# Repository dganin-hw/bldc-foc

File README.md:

# Контроллер BLDC с FOC на STM32

**Своя силовая плата, плата магнитного энкодера и печатный стенд. Дальше тот же канал
ляжет в основу четырёхканального ESC для квадрокоптера.**

[Основная плата](hardware/dev-board/README.md) ·
[Плата энкодера](hardware/encoder-board/README.md) ·
[Стенд](hardware/stand/README.md) ·
[Прошивка](firmware/README.md) ·
[4-in-1 ESC](hardware/esc-4in1/README.md) ·
[Теория FOC](docs/foc-theory.md)

Делаю управление бесщёточным мотором целиком: силовую часть, измерение токов, угол
ротора и векторное управление (FOC). Сначала стенд на один мотор. Когда измерения
сойдутся с расчётом, тот же канал перейдёт в 4-in-1 ESC.

**Сейчас:** обе платы разведены, файлы для производства и перечни компонентов готовы,
механика стенда готова к печати. В прошивке каркас, параметры и тесты. На реальном
моторе ещё не запускал.

## Что готово

| Часть | Что это | Состояние |
|---|---|---|
| [Основная плата](hardware/dev-board/README.md) | STM32G431, DRV8323RS, трёхфазный мост, три шунта, питание и интерфейсы. 108 × 81 мм, 4 слоя | схема, разводка, файлы для производства |
| [Плата энкодера](hardware/encoder-board/README.md) | AS5047P, SPI, питание 3,3 В. 32 × 28 мм, 2 слоя | схема, разводка, файлы для производства |
| [Стенд](hardware/stand/README.md) | основание, крепления плат и мотора, регулируемая опора энкодера, держатель магнита | STL, STEP и инструкция, ещё не напечатан |
| [Прошивка](firmware/README.md) | библиотека на C, конфигурация ШИМ, параметры моторов, тесты | каркас, FOC ещё не написан |
| [4-in-1 ESC](hardware/esc-4in1/README.md) | схема на два STM32G474, распределение выводов, проверка размещения | черновик, не для производства |

Проверки ERC и DRC в KiCad 10 проходят без ошибок на обеих платах. Это проверка
файлов: ток, нагрев и защиты проверяются на собранном стенде.

## Как устроено

Угол ротора приходит с платы энкодера по SPI, токи фаз снимаются с шунтов через
усилители DRV8323. FOC переводит токи в координаты ротора, регулирует их и выдаёт
скважности ШИМ. Драйвер открывает шесть MOSFET трёх полумостов. Авария драйвера
(nFAULT) заведена на вход BKIN таймера и выключает ШИМ аппаратно.

Быстрый цикл привязан к ШИМ 48 кГц и запуску АЦП от того же таймера. Команды и
телеметрия идут вне этого цикла. Энкодер нужен на первых запусках и как эталон, когда
дойдёт до оценки угла без датчика.

Питание стенда 9-16 В, обычно 12 В. На первых включениях ток фазы ограничен 1 А:
этот предел держат прошивка и блок питания, а не плата.

## Основная плата

Четыре слоя: микроконтроллер, драйвер, мост, три канала измерения тока и питание
логики. На плате 36 контрольных площадок: на каждый затвор и исток, ШИМ, токи,
питание. Силовая часть отделена перемычкой, поэтому плату можно запускать по шагам.

[Описание](hardware/dev-board/README.md) ·
[Сборка и первое включение](hardware/dev-board/bring-up.md) ·
[Схема PDF](hardware/dev-board/documentation/SCHEMATIC.pdf) ·
[Файлы для производства](hardware/dev-board/manufacturing/README.md) ·
[CubeMX](hardware/dev-board/cubemx/CubeMX.ioc)

## Плата энкодера

Отдельная маленькая плата, чтобы выставить датчик по оси магнита и подобрать зазор.
Магнит вращается вместе с ротором, плата неподвижна. К основной плате подключается
шестиконтактным кабелем.

[Описание](hardware/encoder-board/README.md) ·
[Схема PDF](hardware/encoder-board/documentation/SCHEMATIC.pdf) ·
[Файлы для производства](hardware/encoder-board/manufacturing/README.md)

## Стенд

Печать из PETG: 11 моделей STL, общая сборка в STEP, пробник посадок, щуп для зазора
и перечень крепежа. Мотор T-Motor MN2212 V2.0 KV920, работа без пропеллера.

[Описание и печать](hardware/stand/README.md) ·
[Сборка и крепёж](hardware/stand/assembly.md) ·
[Лист деталей PDF](hardware/stand/print-layout.pdf)

## Основные компоненты

| Компонент | Зачем |
|---|---|
| STM32G431CBT6 | Cortex-M4F 170 МГц, таймер TIM1 с dead-time и аварийным входом, два АЦП с запуском от таймера |
| DRV8323RSRGZT | драйвер шести затворов, три усилителя тока, диагностика по SPI, свой понижающий преобразователь |
| 6 × PSMN7R0-60YS,115 | N-MOSFET моста, 60 В, корпус LFPAK56 |
| 3 × WSK2512R0200FEA | шунты 20 мОм с отдельными измерительными выводами |
| AS5047P-ATSM | магнитный энкодер, 14 бит, на отдельной плате |
| AP2112K-3.3TRG1 | 3,3 В для логики |
| SRN6045TA-330M и SS16 | дроссель и диод понижающего преобразователя |
| IRFR5305TRPBF | защита входа от переполюсовки |
| SMBJ18A | TVS-диод от коротких выбросов. Энергию торможения он не поглощает |
| NCP18XH103F03RB | термистор, температура платы |
| Eaton BK1/S501-2-R | предохранитель 2 А на входе. Мост он не защищает |

Полный перечень с артикулами и кодами LCSC: [основная плата](hardware/dev-board/manufacturing/bom/BOM.csv),
[плата энкодера](hardware/encoder-board/manufacturing/bom/BOM.csv).

## Прошивка

Пишу на C99. Математика FOC отделена от регистров, поэтому один и тот же код
собирается на ПК для тестов и кросс-компилятором под Cortex-M4F. В GitHub Actions на
каждый push запускаются тесты на ПК и сборка под ARM.

Нужны CMake 3.20 или новее и компилятор C. Из корня репозитория:

```sh
cmake -S firmware -B build -DCMAKE_BUILD_TYPE=Debug
cmake --build build --parallel
ctest --test-dir build --output-on-failure
```

Сейчас готовы вспомогательные функции, конфигурация ШИМ, параметры моторов и тесты.
Преобразования Кларка и Парка, PI-регуляторы, модулятор, модель мотора, драйверы и
наблюдатель на очереди.

[Подробнее о прошивке](firmware/README.md) ·
[Архитектура прошивки](docs/firmware-architecture.md) ·
[Теория FOC](docs/foc-theory.md)

## План

- [ ] **Этап 0. FOC на модели мотора.** Каркас, тесты и CI уже есть. Дальше
  преобразования, SVPWM, PI и модель мотора на ПК.
- [x] **Этап 1. Основная плата и плата энкодера.** Схема, разводка, файлы для
  производства, механика стенда.
- [ ] **Этап 2. Запуск платы и FOC с энкодером.** Питание, защиты, калибровка токов,
  окно АЦП, токовый контур на стенде, нагрев.
- [ ] **Этап 3. Работа без датчика.** Наблюдатель с PLL, сравнение оценки угла с
  энкодером, переход на дрон-мотор.
- [ ] **Этап 4. Интерфейс дрона.** Приём DShot600, телеметрия, защиты, проверка с
  покупным полётным контроллером.
- [ ] **Этап 5. Плата 4-in-1.** Сначала один канал, потом остальные три.
- [ ] **Этап 6. Квадрокоптер.** Проверки на земле без пропеллеров, полёт на привязи.

Почему полётный контроллер покупной и как всё связано, описано в
[архитектуре системы](docs/system-architecture.md). Правила безопасности на стенде:
[docs/safety.md](docs/safety.md).

## Структура репозитория

```text
bldc-foc/
├── assets/                картинки для README
├── docs/                  теория FOC, архитектура, план выводов, безопасность
├── firmware/              библиотека на C, тесты и CMake
├── hardware/
│   ├── dev-board/         основная плата: KiCad, CubeMX, документация, производство
│   ├── encoder-board/     плата энкодера
│   ├── stand/             испытательный стенд: STL, STEP, сборка
│   └── esc-4in1/          черновик четырёхканального ESC
├── sources/               ссылки на документацию производителей
└── .github/workflows/     сборка и тесты в GitHub Actions
```

Проекты KiCad открываются в KiCad 10. Лицензия на проект пока не выбрана,
сторонние материалы описаны в [LICENSES.md](LICENSES.md), документация производителей
в [sources/README.md](sources/README.md).

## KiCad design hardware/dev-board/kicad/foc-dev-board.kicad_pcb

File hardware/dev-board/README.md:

# Основная плата

Плата управления одним бесколлекторным мотором: STM32G431, драйвер DRV8323RS,
трёхфазный мост на шести MOSFET и три шунта для измерения токов. Всё, что нужно
мерить на стенде, выведено на контрольные площадки.

*3D-вид из KiCad. Шунты R30-R32 показаны без 3D-модели.*

*Нижняя сторона по Gerber-файлам: распиновка разъёмов на шелкографии.*

## Коротко

| Параметр | Значение |
|---|---|
| Размер | 108 × 81 мм, 4 слоя, FR-4 1,6 мм |
| Компоненты | 149 позиций, из них 109 устанавливаются, 36 контрольных площадок и 4 отверстия M3 |
| Трассировка | 2598 сегментов дорожек, 300 переходных отверстий, земля на всех четырёх слоях |
| Питание | 12 В номинально, рабочий диапазон 9-16 В |
| Ток фазы на первых запусках | до 1 А (ограничение в прошивке и на блоке питания) |
| Измерение тока | шунты 20 мОм, усиление 40, 0,8 В/А, линейный диапазон около ±1,75 А |
| ШИМ | 48 кГц, TIM1, центрированный, dead-time около 400 нс |

## Схема по листам

| Лист | Что на нём |
|---|---|
| 01 Power | вход, предохранитель 2 А, защита от переполюсовки, понижающий преобразователь 5 В, LDO 3,3 В |
| 02 MCU | STM32G431CBT6 в LQFP48, развязка питания, BOOT0, RESET, светодиоды |
| 03 Driver | DRV8323RS, зарядовый насос, SPI, ENABLE, nFAULT, фильтры АЦП |
| 04 Inverter | шесть MOSFET PSMN7R0-60YS, затворные резисторы, три четырёхвыводных шунта |
| 05 Interfaces | мотор, энкодер, SWD, UART, DShot, делитель напряжения шины, термистор |
| 06 Testpoints | 36 контрольных площадок и четыре крепёжных отверстия |

Назначение выводов STM32 описано в [плане выводов](../../docs/pin-plan.md),
конфигурация периферии лежит в [`cubemx/CubeMX.ioc`](cubemx/CubeMX.ioc).

## Как устроено питание

`J1 → F1 → Q7 → VIN_PROTECTED`: вход через предохранитель 2 А и P-MOSFET от переполюсовки.
От `VIN_PROTECTED` работает понижающий преобразователь DRV8323 (5 В) и дальше LDO AP2112
(3,3 В для STM32 и энкодера).

- **JP1** подключает `VIN_PROTECTED` к шине `VM`, то есть к мосту и питанию драйвера.
  С открытой JP1 можно спокойно проверить питание логики и прошить МК.
- **JP2** разрешает управлять ENABLE драйвера с МК. Без перемычки резистор R14 держит
  ENABLE в нуле.
- **SW2** отключает драйвер, пока кнопка нажата. Это не защёлка: после отпускания
  прошивка не должна включаться сама.
- **nFAULT** драйвера заведён на PA12 и на вход BKIN таймера TIM1, чтобы ШИМ выключался
  аппаратно.
- **J7** выводит шину `VM` для внешней нагрузки при опытах с торможением. TVS-диод
  SMBJ18A гасит только короткие выбросы и не рассчитан на энергию торможения.

## Разъёмы

| Разъём | Назначение |
|---|---|
| J1 | питание 12 В |
| J2 | фазы мотора A, B, C |
| J3 | энкодер: 3,3 В, GND, SCK, MISO, MOSI, CS |
| J4 | SWD: VTREF, GND, SWDIO, SWCLK, NRST |
| J5 | UART: 3,3 В, GND, TX, RX |
| J6 | DShot и GND |
| J7 | шина VM для внешней нагрузки |

Все сигналы 3,3 В. Контакты питания на разъёмах - выход платы или VTREF, а не вход.

## Контрольные площадки

| Площадки | Что на них |
|---|---|
| TP1-TP3 | GND |
| TP4, TP5 | VIN_PROTECTED и VM, до и после JP1 |
| TP6, TP7, TP8 | 5 В, 3,3 В и аналоговые 3,3 В |
| TP9-TP12 | ENABLE, nFAULT, сигнал замера времени цикла, MISO |
| TP13-TP18 | шесть сигналов ШИМ от STM32 |
| TP19, TP20, TP21 | сигналы токов фаз A, B, C на входах АЦП |
| TP22, TP23 | напряжение шины и температура |
| TP24 | внутреннее питание DVDD драйвера |
| TP25-TP36 | затвор и исток верхнего и нижнего ключа каждой фазы |

Землю обычного осциллографа подключать только к GND, а не к фазе или истоку верхнего
ключа. Для таких точек нужен дифференциальный щуп.

## Файлы

- [`kicad/`](kicad/) - проект KiCad 10: схема, плата и библиотеки проекта. Открывать
  `foc-dev-board.kicad_pro`, копировать нужно всю папку.
- [`documentation/SCHEMATIC.pdf`](documentation/SCHEMATIC.pdf) - схема, 7 листов.
- [`documentation/ASSEMBLY.pdf`](documentation/ASSEMBLY.pdf) - сборочный чертёж, верхняя сторона.
- [`manufacturing/`](manufacturing/) - Gerber, сверловка, перечень компонентов и координаты.
- [`mechanical/foc-dev-board.step`](mechanical/foc-dev-board.step) - 3D-модель платы с компонентами.
- [`cubemx/`](cubemx/) - конфигурация STM32CubeMX и отчёт по ней.

## Что проверить на собранной плате

Проверки ERC и DRC в KiCad проходят без ошибок, но это проверка файлов, а не работы платы.
Перед запуском мотора нужно:

1. **Ток и защиту.** Предел 1 А задаётся прошивкой и блоком питания. Минимальный порог
   защиты DRV8323 (0,25 В на шунте) с шунтом 20 мОм соответствует 12,5 А, поэтому он не
   заменяет программный предел. Предохранитель 2 А стоит на входе и фазный ток не ограничивает.
2. **Окно АЦП.** Ток A и C измеряет ADC1, ток B - ADC2, это не одновременная выборка.
   При скважности 97% нижний ключ открыт всего 625 нс, а dead-time 400 нс плюс
   установление усилителя (при усилении 40 по документации около 1,2 мкс) туда не
   помещаются. Окно выборки и предел скважности нужно проверить осциллографом.
3. **Включение и аварийное отключение.** Запрет самозапуска, ручное повторное включение
   после аварии, работа BKIN и поведение при остановке отладчиком.
4. **Коммутацию.** Начать с умеренного тока затворов DRV8323, проверить напряжение на
   затворах, звон и отсутствие сквозного тока.
5. **Нагрев.** LDO AP2112 при 150 мА рассеивает около 0,25 Вт, ключи и шунты проверить
   термопарой на реальном токе.

Пошаговый порядок описан в [памятке по сборке и первому включению](bring-up.md).

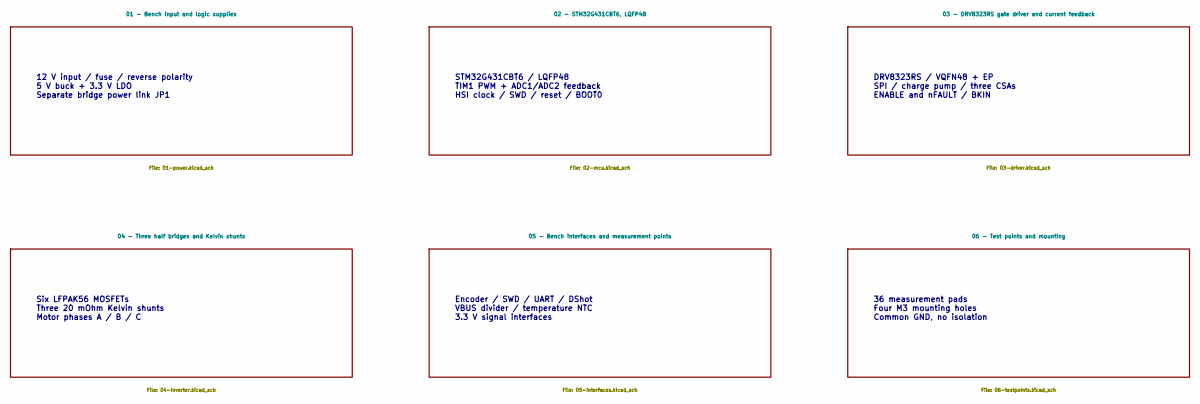
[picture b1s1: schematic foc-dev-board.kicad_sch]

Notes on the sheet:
12 V input / fuse / reverse polarity 5 V buck + 3.3 V LDO Separate bridge power link JP1
Encoder / SWD / UART / DShot VBUS divider / temperature NTC 3.3 V signal interfaces
Six LFPAK56 MOSFETs Three 20 mOhm Kelvin shunts Motor phases A / B / C
36 measurement pads Four M3 mounting holes Common GND, no isolation
DRV8323RS / VQFN48 + EP SPI / charge pump / three CSAs ENABLE and nFAULT / BKIN
STM32G431CBT6 / LQFP48 TIM1 PWM + ADC1/ADC2 feedback HSI clock / SWD / reset / BOOT0

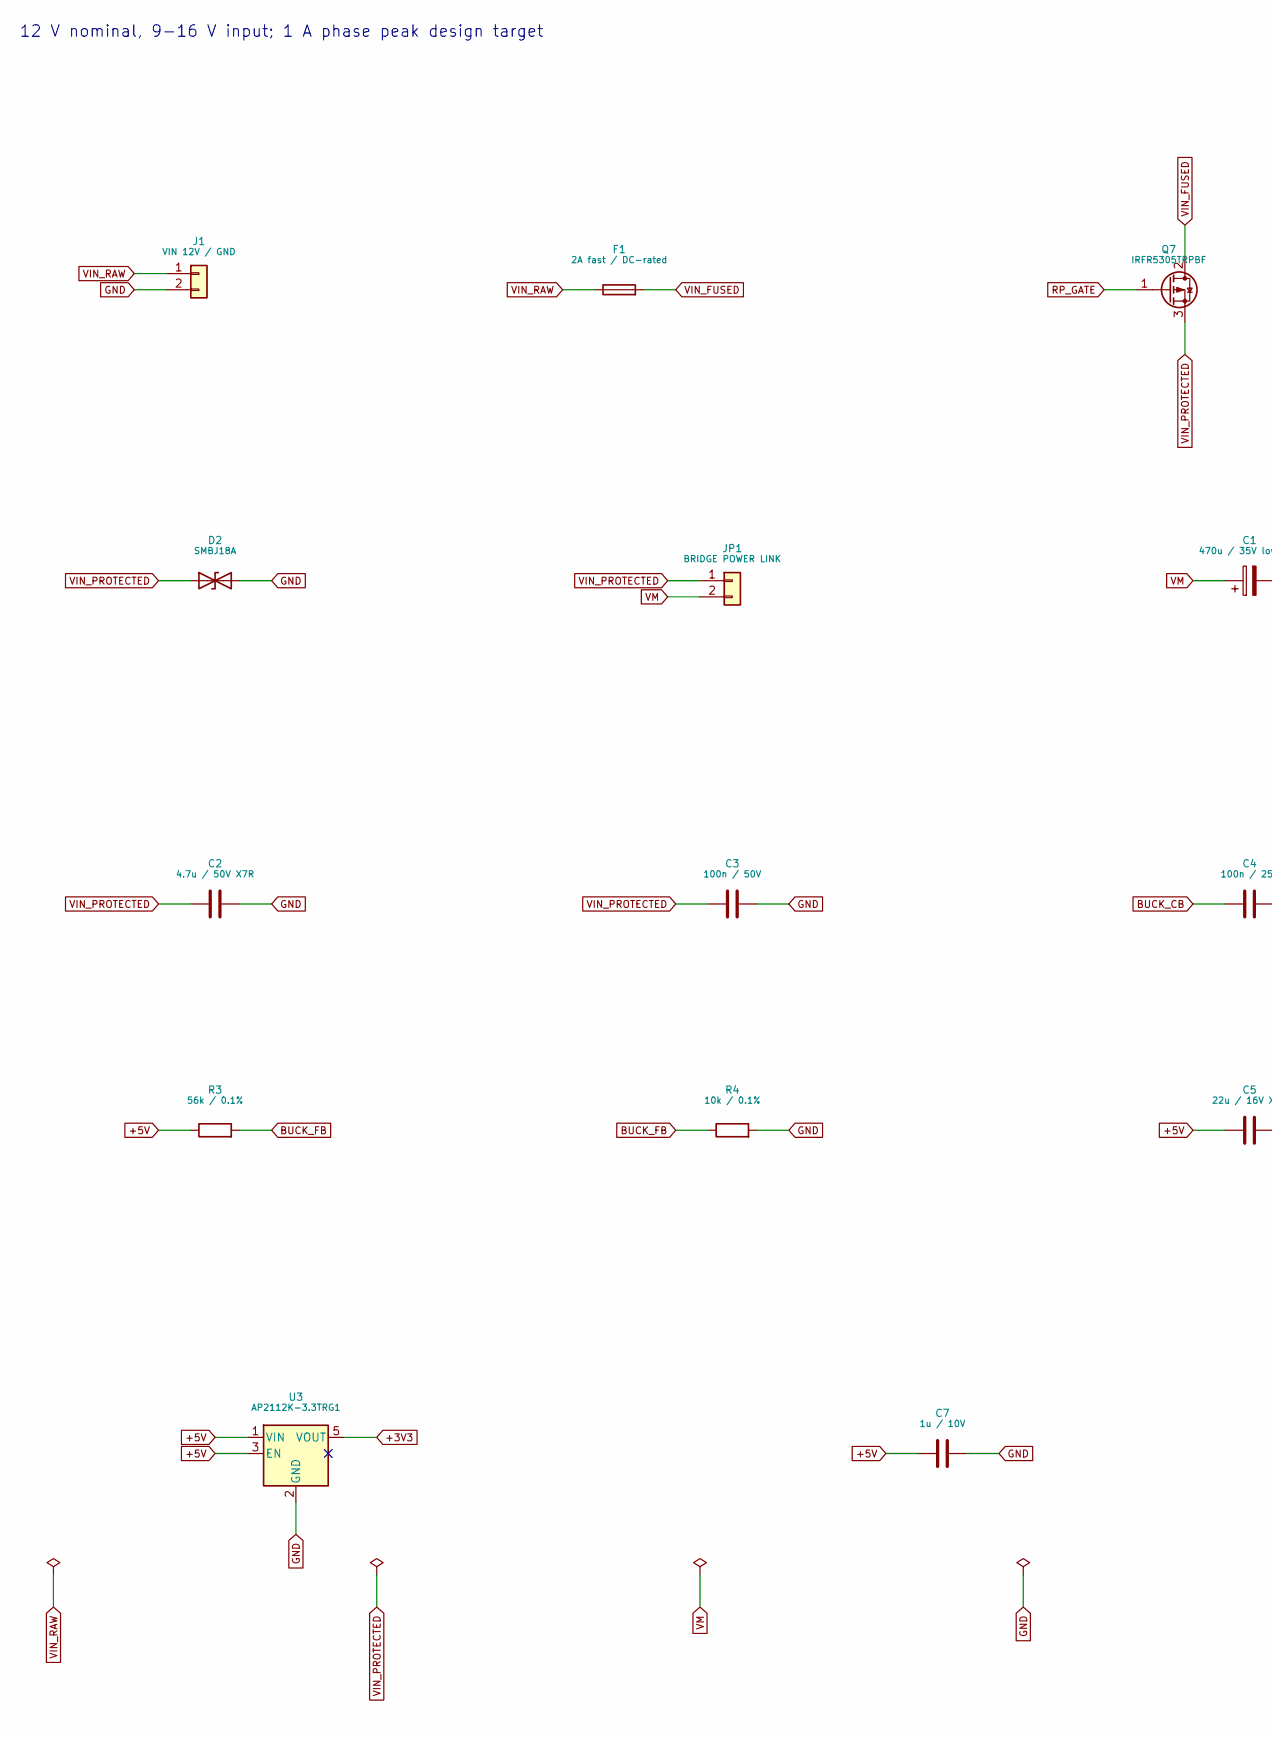
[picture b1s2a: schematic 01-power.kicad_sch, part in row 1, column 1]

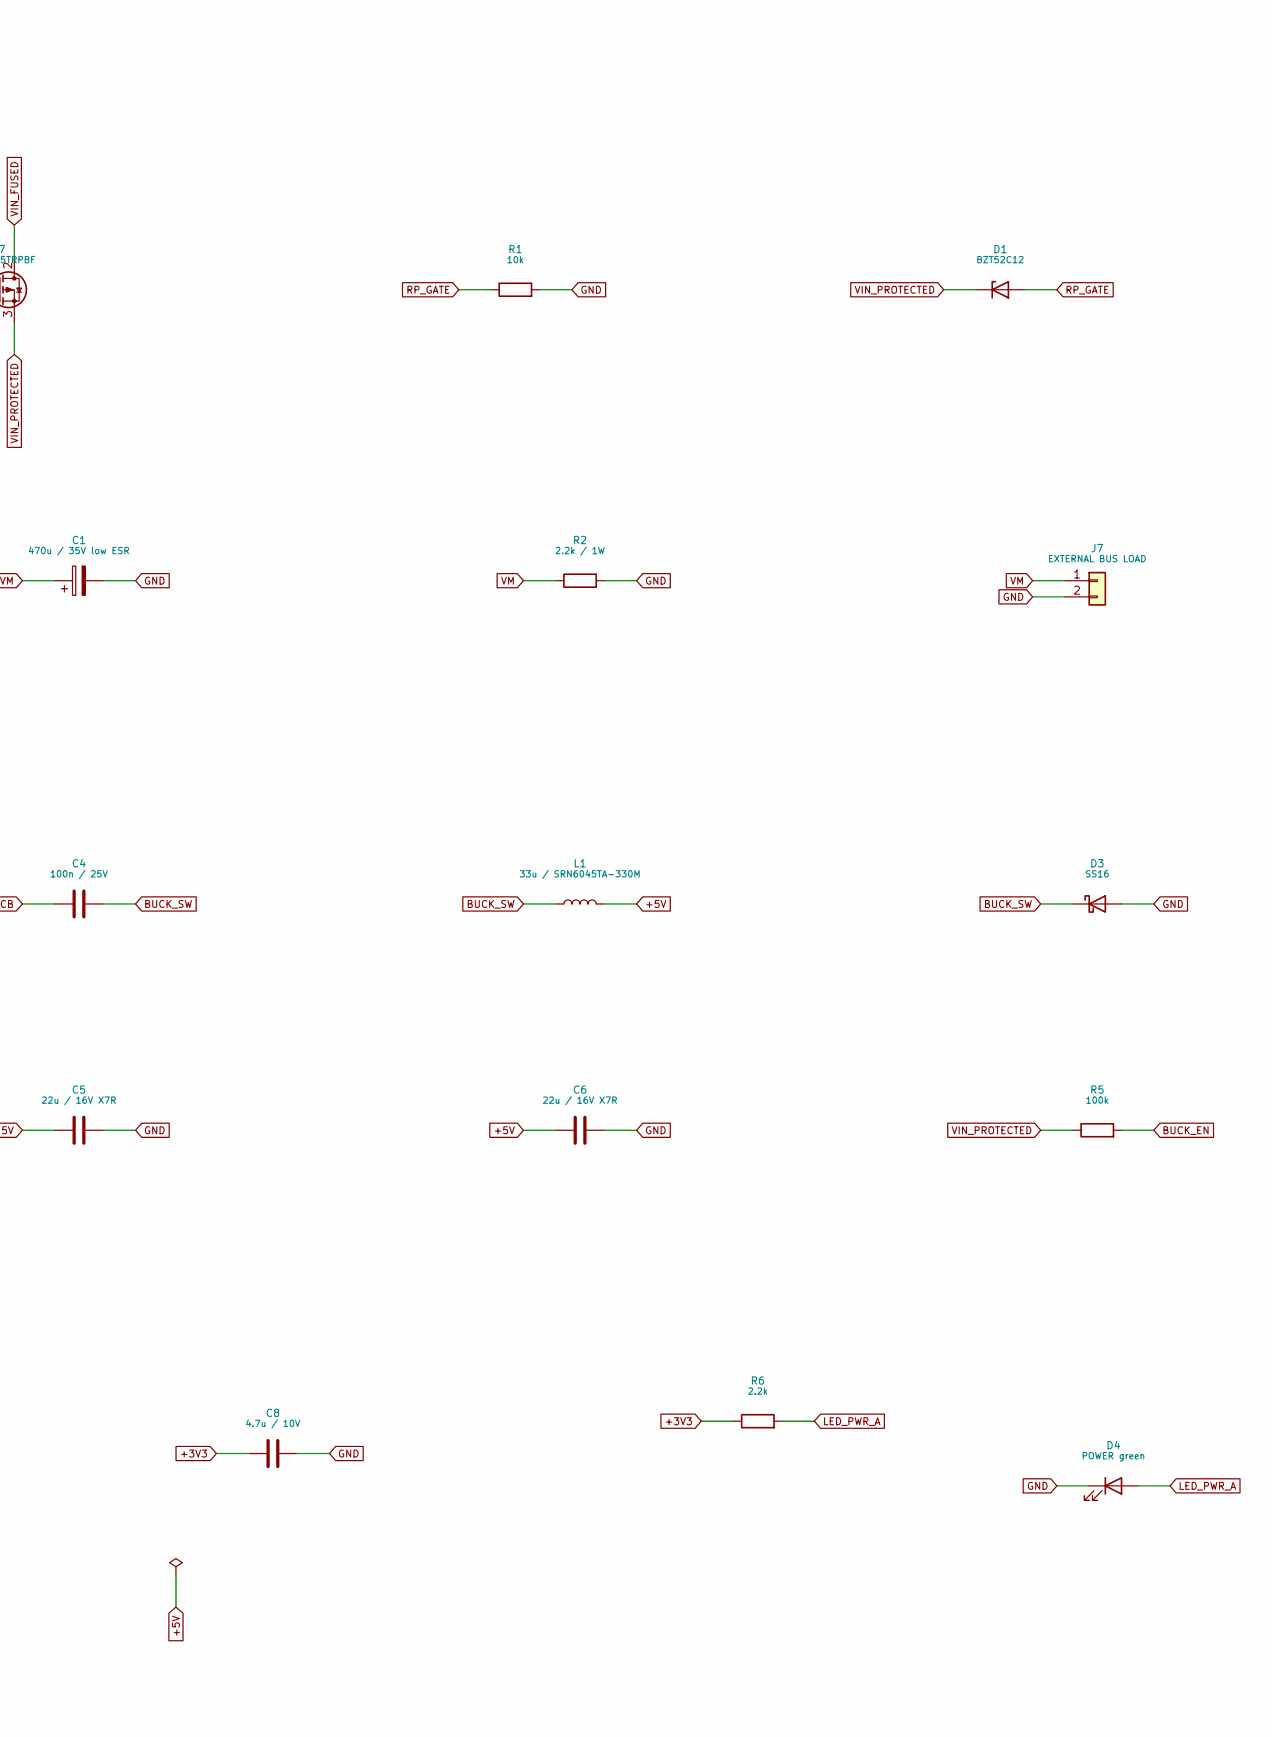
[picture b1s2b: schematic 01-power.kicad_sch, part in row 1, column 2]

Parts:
C1: 470u / 35V low ESR; CP_Radial_D10.0mm_P5.00mm; MPN EEUFR1V471
C2: 4.7u / 50V X7R; C_1210_3225Metric
C3: 100n / 50V; C_0603_1608Metric
C4: 100n / 25V; C_0603_1608Metric
C5, C6: 22u / 16V X7R; C_1210_3225Metric
C7: 1u / 10V; C_0603_1608Metric
C8: 4.7u / 10V; C_0805_2012Metric
D1: BZT52C12; D_SOD-123; MPN BZT52C12-7-F
D2: SMBJ18A; D_SMB; MPN SMBJ18A
D3: SS16; D_SMA; MPN SS16
D4: POWER green; LED_0603_1608Metric
F1: 2A fast / DC-rated; Fuseholder_Clip-5x20mm_Littelfuse_111_Inline_P20.00x5.00mm_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; MPN 01110005MR x2
J1: VIN 12V / GND; TerminalBlock_Phoenix_MKDS-1,5-2-5.08_1x02_P5.08mm_Horizont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; MPN 1715721
J7: EXTERNAL BUS LOAD; TerminalBlock_Phoenix_MKDS-1,5-2-5.08_1x02_P5.08mm_Horizont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; MPN 1715721
JP1: BRIDGE POWER LINK; PinHeader_1x02_P2.54mm_Vertical
L1: 33u / SRN6045TA-330M; L_Bourns_SRN6045TA; MPN SRN6045TA-330M
Q7: IRFR5305TRPBF; TO-252-2; MPN IRFR5305TRPBF
R1: 10k; R_0603_1608Metric
R2: 2.2k / 1W; R_2512_6332Metric
R3: 56k / 0.1%; R_0603_1608Metric
R4: 10k / 0.1%; R_0603_1608Metric
R5: 100k; R_0603_1608Metric
R6: 2.2k; R_0603_1608Metric
U3: AP2112K-3.3TRG1; SOT-23-5; MPN AP2112K-3.3TRG1

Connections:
+3V3: C8.1, R6.1, U3.5 (VOUT); also elsewhere on the board
+5V: C5.1, C6.1, C7.1, L1.2, R3.1, U3.1 (VIN), U3.3 (EN); also elsewhere on the board
BUCK_CB: C4.1; also elsewhere on the board
BUCK_EN: R5.2; also elsewhere on the board
BUCK_FB: R3.2, R4.1; also elsewhere on the board
BUCK_SW: C4.2, D3.1 (K), L1.1; also elsewhere on the board
GND: C1.2, C2.2, C3.2, C5.2, C6.2, C7.2, C8.2, D2.2 (A2), D3.2 (A), D4.1 (K), J1.2, J7.2, R1.2, R2.2, R4.2, U3.2 (GND); also elsewhere on the board
LED_PWR_A: D4.2 (A), R6.2
RP_GATE: D1.2 (A), Q7.1 (G), R1.1
VIN_FUSED: F1.2, Q7.2 (D)
VIN_PROTECTED: C2.1, C3.1, D1.1 (K), D2.1 (A1), JP1.1, Q7.3 (S), R5.1; also elsewhere on the board
VIN_RAW: F1.1, J1.1
VM: C1.1, J7.1, JP1.2, R2.1; also elsewhere on the board

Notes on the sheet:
12 V nominal, 9-16 V input; 1 A phase peak design target

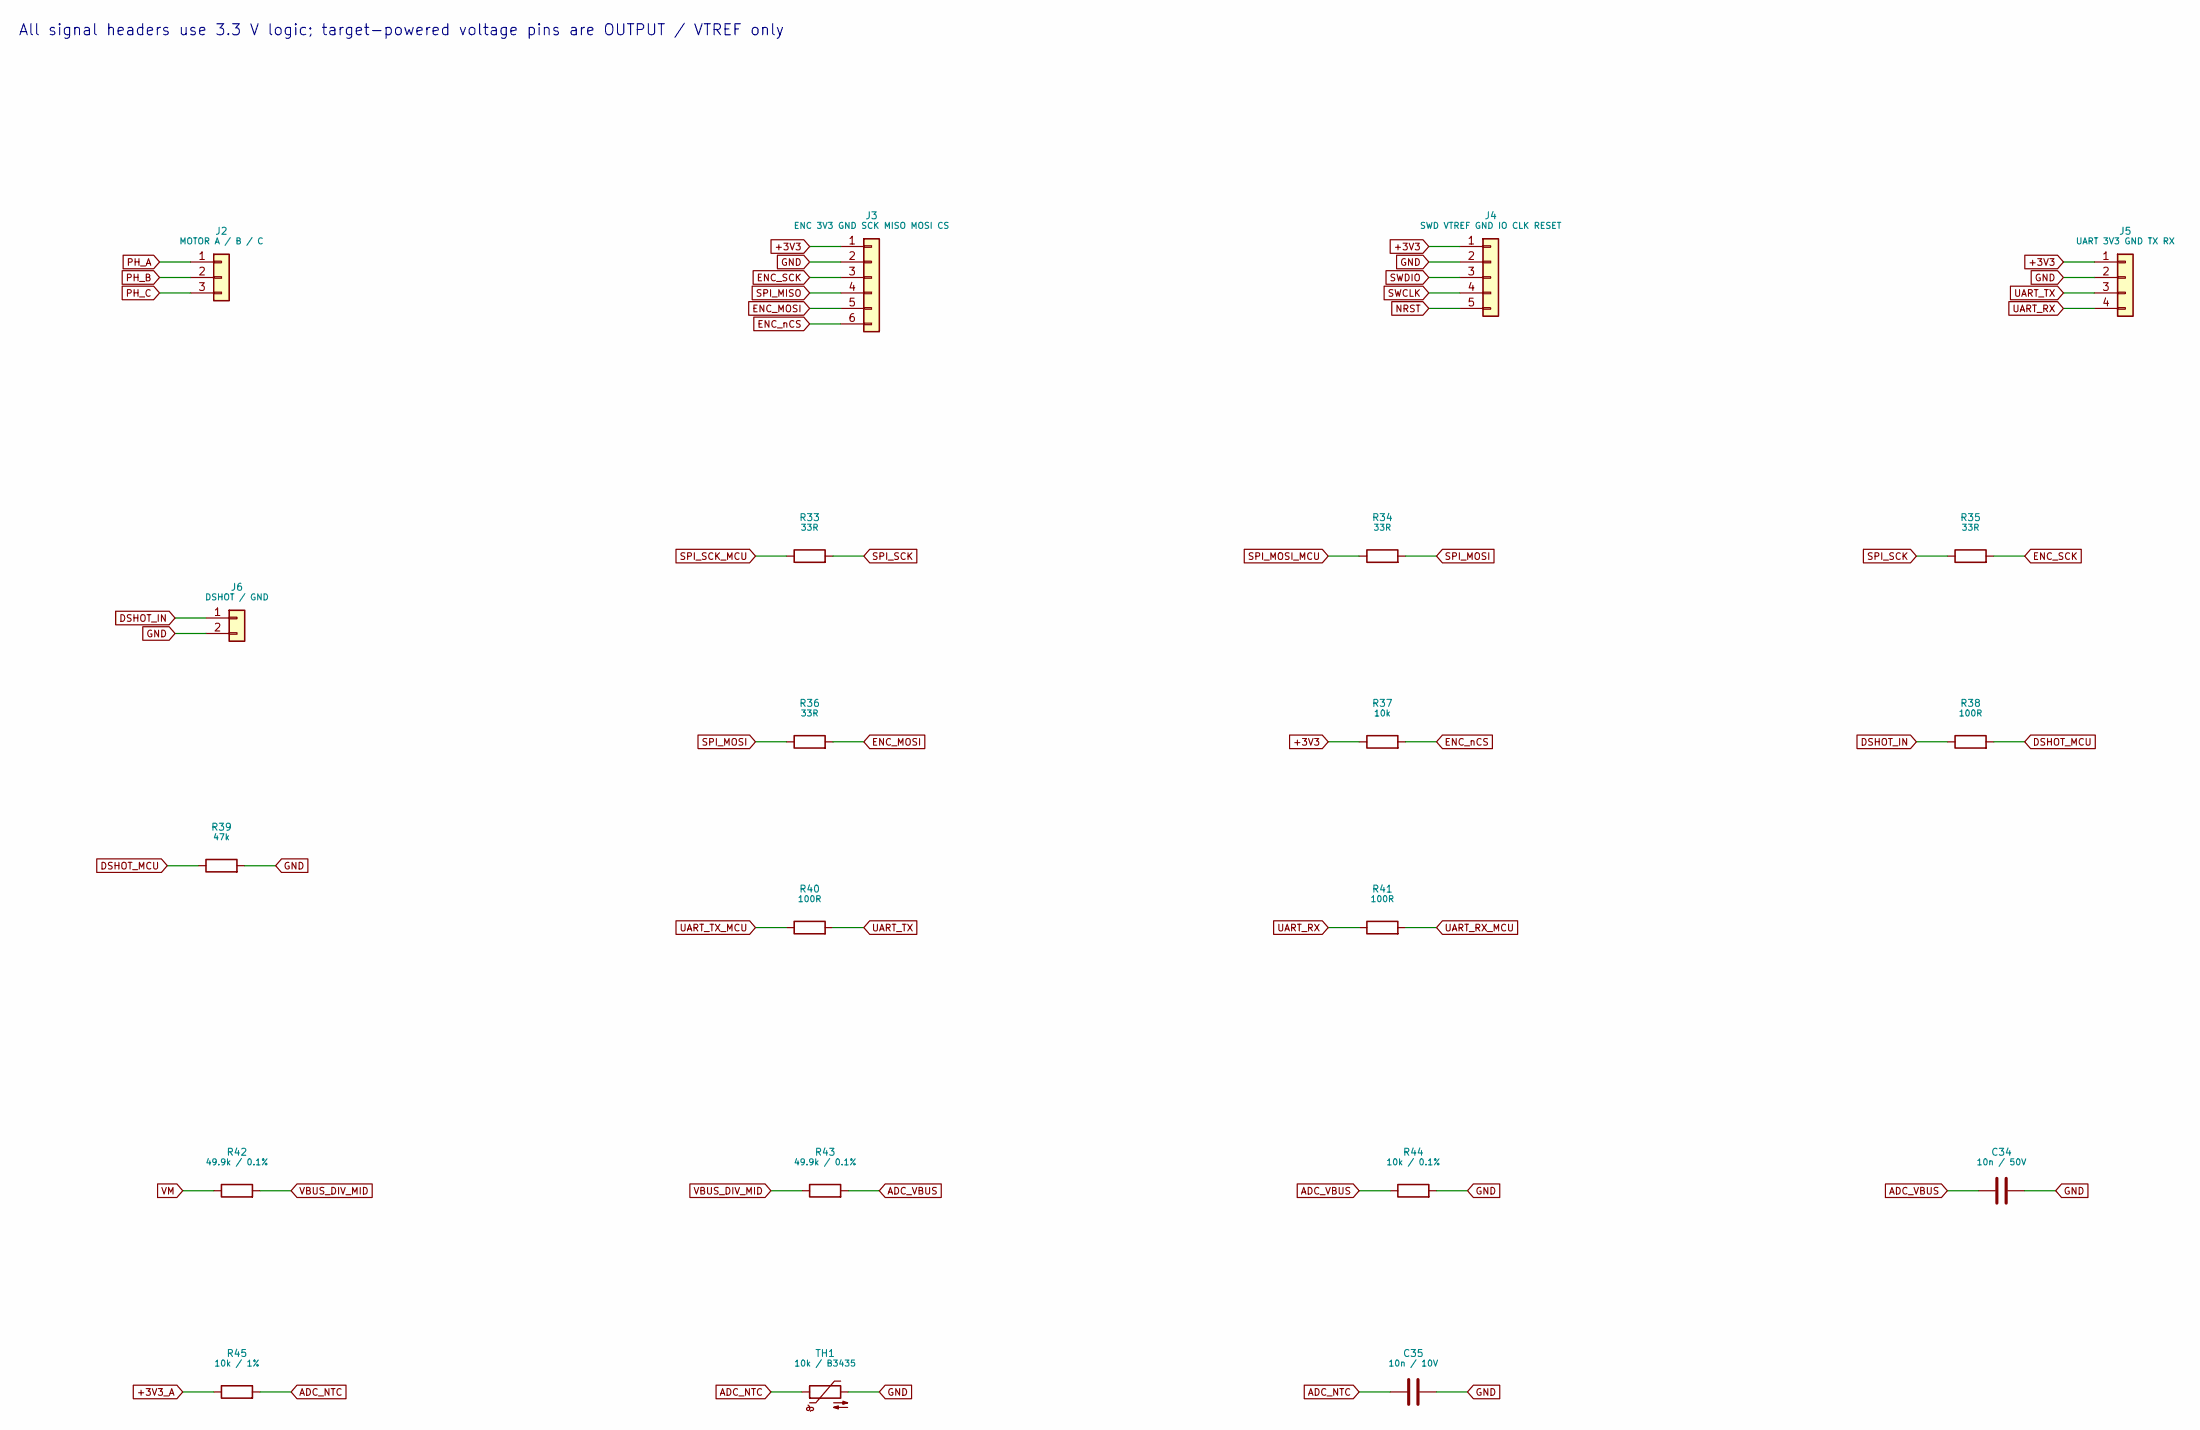
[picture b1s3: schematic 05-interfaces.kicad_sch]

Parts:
C34: 10n / 50V; C_0603_1608Metric
C35: 10n / 10V; C_0603_1608Metric
J2: MOTOR A / B / C; TerminalBlock_Phoenix_MKDS-1,5-3-5.08_1x03_P5.08mm_Horizont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; MPN 1715734
J3: ENC 3V3 GND SCK MISO MOSI CS; PinHeader_1x06_P2.54mm_Vertical
J4: SWD VTREF GND IO CLK RESET; PinHeader_1x05_P2.54mm_Vertical
J5: UART 3V3 GND TX RX; PinHeader_1x04_P2.54mm_Vertical
J6: DSHOT / GND; PinHeader_1x02_P2.54mm_Vertical
R33, R34, R35, R36: 33R; R_0603_1608Metric
R37: 10k; R_0603_1608Metric
R38, R40, R41: 100R; R_0603_1608Metric
R39: 47k; R_0603_1608Metric
R42, R43: 49.9k / 0.1%; R_0603_1608Metric
R44: 10k / 0.1%; R_0603_1608Metric
R45: 10k / 1%; R_0603_1608Metric
TH1: 10k / B3435; R_0603_1608Metric; MPN NCP18XH103F03RB

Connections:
+3V3: J3.1, J4.1, J5.1, R37.1; also elsewhere on the board
+3V3_A: R45.1; also elsewhere on the board
ADC_NTC: C35.1, R45.2, TH1.1; also elsewhere on the board
ADC_VBUS: C34.1, R43.2, R44.1; also elsewhere on the board
DSHOT_IN: J6.1, R38.1
DSHOT_MCU: R38.2, R39.1; also elsewhere on the board
ENC_MOSI: J3.5, R36.2
ENC_SCK: J3.3, R35.2
ENC_nCS: J3.6, R37.2; also elsewhere on the board
GND: C34.2, C35.2, J3.2, J4.2, J5.2, J6.2, R39.2, R44.2, TH1.2; also elsewhere on the board
NRST: J4.5; also elsewhere on the board
PH_A: J2.1; also elsewhere on the board
PH_B: J2.2; also elsewhere on the board
PH_C: J2.3; also elsewhere on the board
SPI_MISO: J3.4; also elsewhere on the board
SPI_MOSI: R34.2, R36.1; also elsewhere on the board
SPI_MOSI_MCU: R34.1; also elsewhere on the board
SPI_SCK: R33.2, R35.1; also elsewhere on the board
SPI_SCK_MCU: R33.1; also elsewhere on the board
SWCLK: J4.4; also elsewhere on the board
SWDIO: J4.3; also elsewhere on the board
UART_RX: J5.4, R41.1
UART_RX_MCU: R41.2; also elsewhere on the board
UART_TX: J5.3, R40.2
UART_TX_MCU: R40.1; also elsewhere on the board
VBUS_DIV_MID: R42.2, R43.1
VM: R42.1; also elsewhere on the board

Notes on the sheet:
All signal headers use 3.3 V logic; target-powered voltage pins are OUTPUT / VTREF only

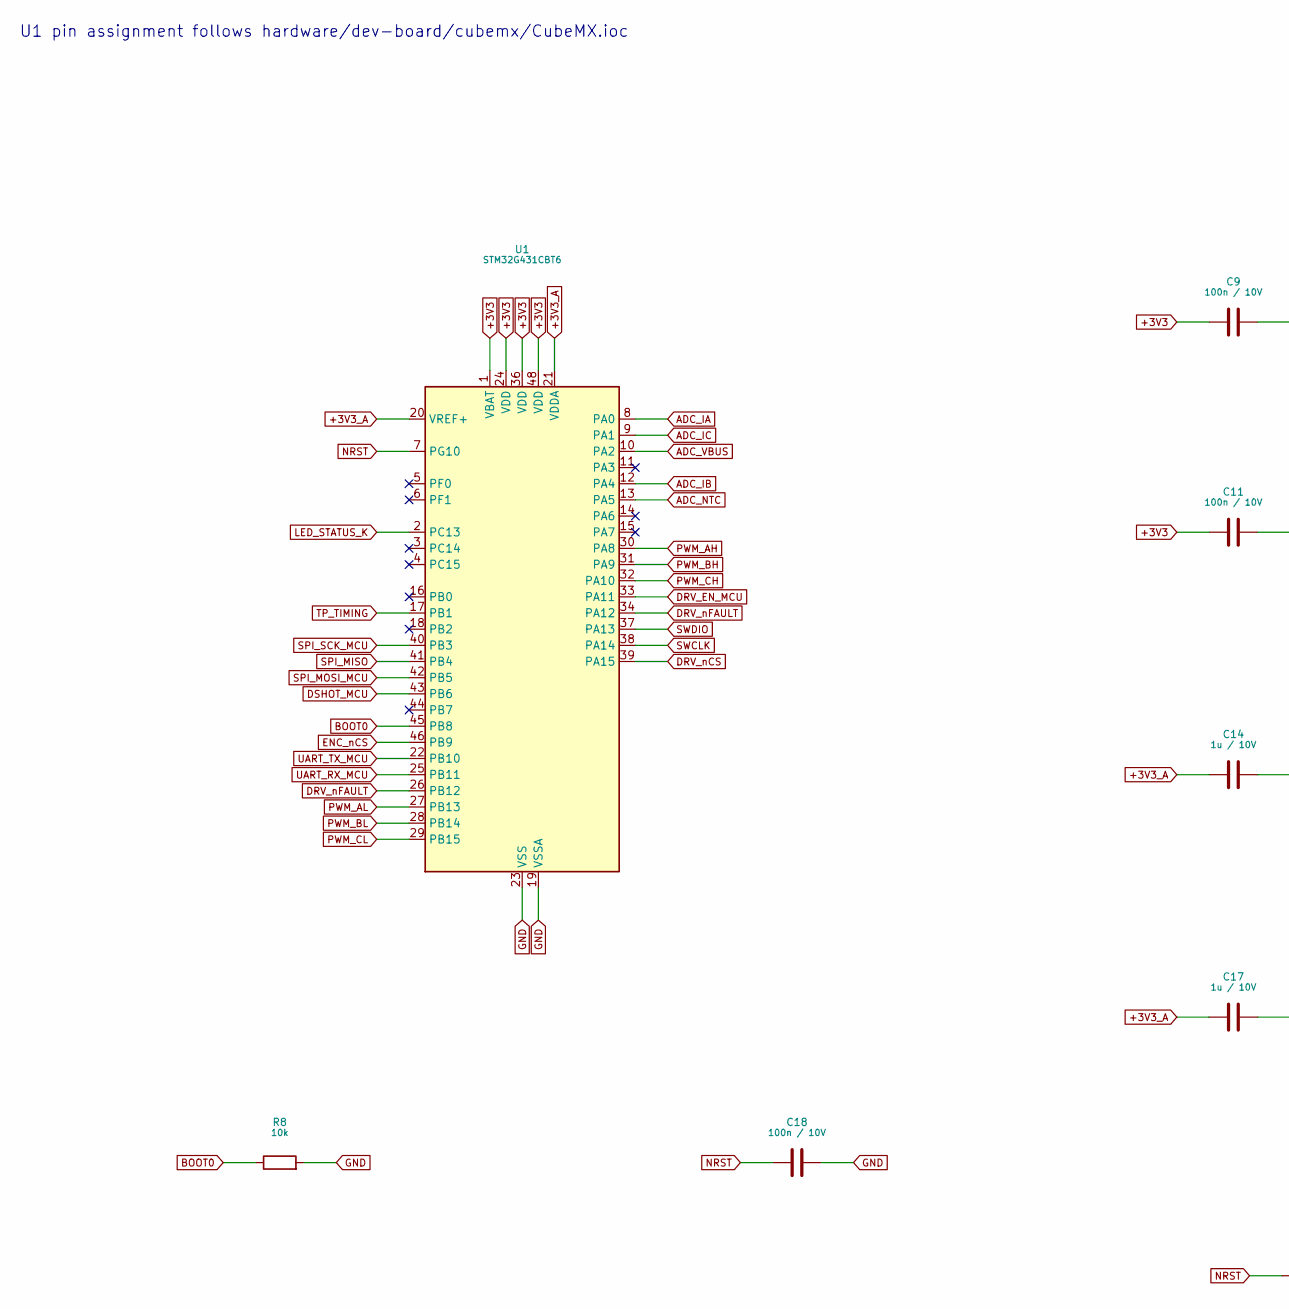
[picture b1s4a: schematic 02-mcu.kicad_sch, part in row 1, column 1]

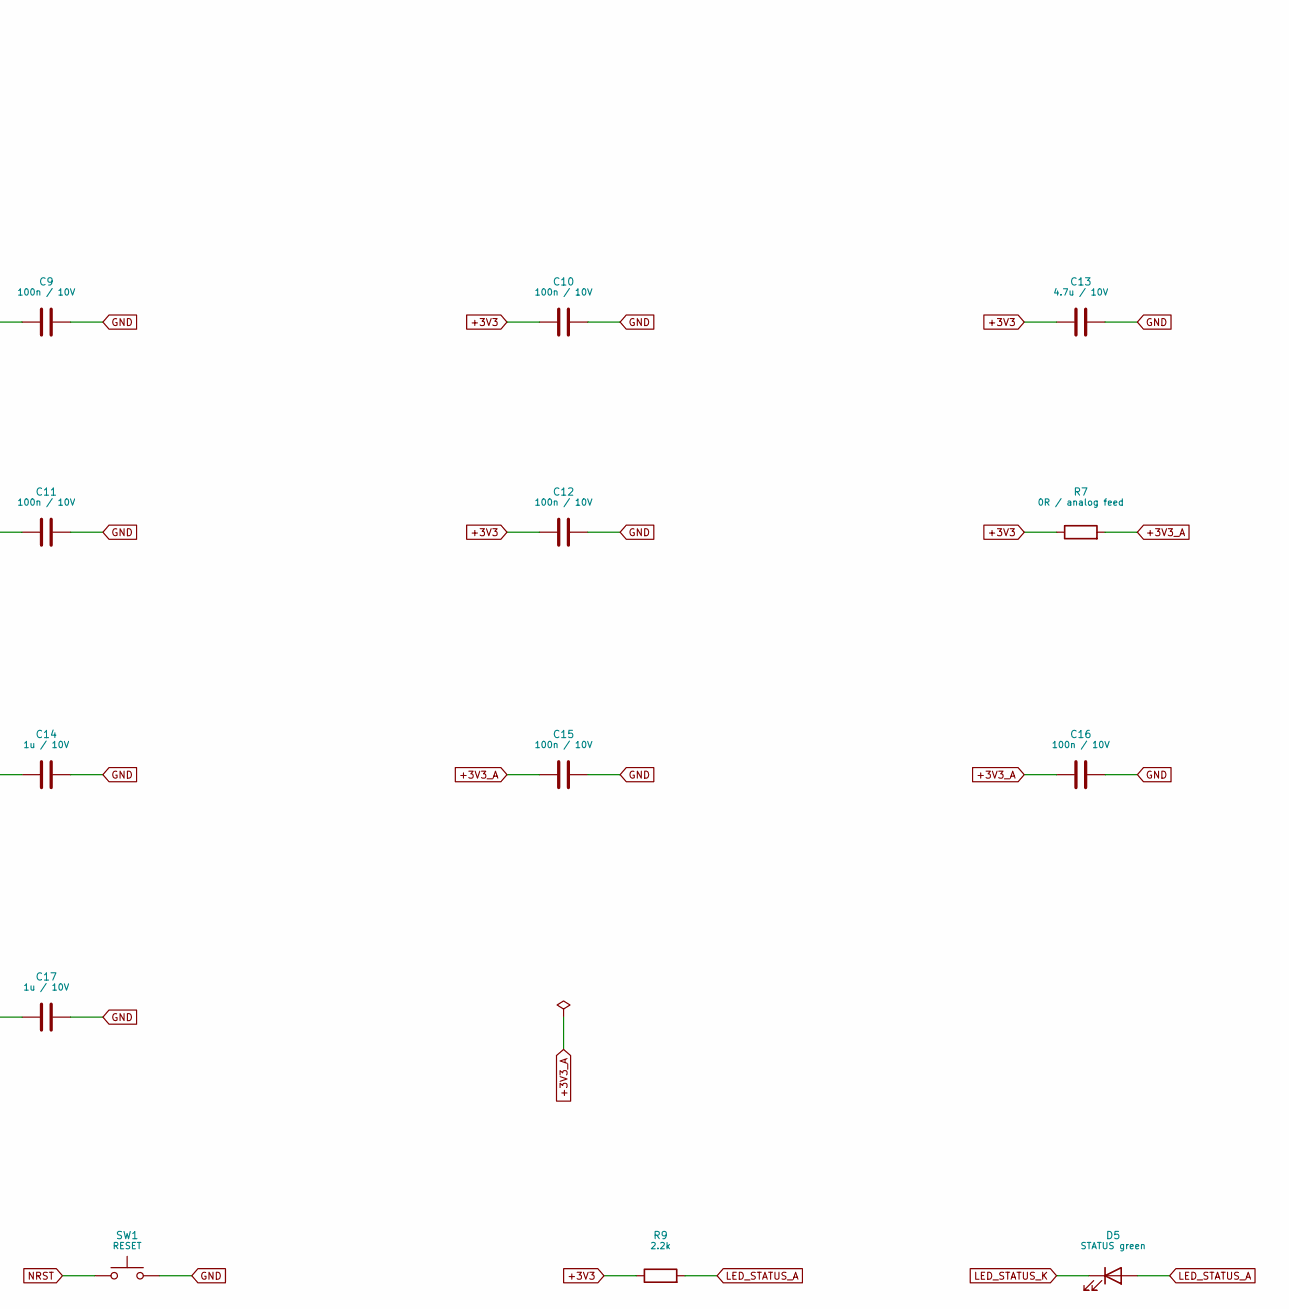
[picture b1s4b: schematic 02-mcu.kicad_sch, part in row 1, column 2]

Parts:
C9, C10, C11, C12, C15, C16, C18: 100n / 10V; C_0603_1608Metric
C13: 4.7u / 10V; C_0805_2012Metric
C14, C17: 1u / 10V; C_0603_1608Metric
D5: STATUS green; LED_0603_1608Metric
R7: 0R / analog feed; R_0603_1608Metric
R8: 10k; R_0603_1608Metric
R9: 2.2k; R_0603_1608Metric
SW1: RESET; SW_SPST_TL3342; MPN TL3342F160QG
U1: STM32G431CBT6; LQFP-48_7x7mm_P0.5mm; MPN STM32G431CBT6

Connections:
+3V3: C9.1, C10.1, C11.1, C12.1, C13.1, R7.1, R9.1, U1.1 (VBAT), U1.24 (VDD), U1.36 (VDD), U1.48 (VDD); also elsewhere on the board
+3V3_A: C14.1, C15.1, C16.1, C17.1, R7.2, U1.20 (VREF+), U1.21 (VDDA); also elsewhere on the board
ADC_IA: U1.8 (PA0); also elsewhere on the board
ADC_IB: U1.12 (PA4); also elsewhere on the board
ADC_IC: U1.9 (PA1); also elsewhere on the board
ADC_NTC: U1.13 (PA5); also elsewhere on the board
ADC_VBUS: U1.10 (PA2); also elsewhere on the board
BOOT0: R8.1, U1.45 (PB8)
DRV_EN_MCU: U1.33 (PA11); also elsewhere on the board
DRV_nCS: U1.39 (PA15); also elsewhere on the board
DRV_nFAULT: U1.26 (PB12), U1.34 (PA12); also elsewhere on the board
DSHOT_MCU: U1.43 (PB6); also elsewhere on the board
ENC_nCS: U1.46 (PB9); also elsewhere on the board
GND: C9.2, C10.2, C11.2, C12.2, C13.2, C14.2, C15.2, C16.2, C17.2, C18.2, R8.2, SW1.2, U1.19 (VSSA), U1.23 (VSS), U1.35 (VSS), U1.47 (VSS); also elsewhere on the board
LED_STATUS_A: D5.2 (A), R9.2
LED_STATUS_K: D5.1 (K), U1.2 (PC13)
NRST: C18.1, SW1.1, U1.7 (PG10); also elsewhere on the board
PWM_AH: U1.30 (PA8); also elsewhere on the board
PWM_AL: U1.27 (PB13); also elsewhere on the board
PWM_BH: U1.31 (PA9); also elsewhere on the board
PWM_BL: U1.28 (PB14); also elsewhere on the board
PWM_CH: U1.32 (PA10); also elsewhere on the board
PWM_CL: U1.29 (PB15); also elsewhere on the board
SPI_MISO: U1.41 (PB4); also elsewhere on the board
SPI_MOSI_MCU: U1.42 (PB5); also elsewhere on the board
SPI_SCK_MCU: U1.40 (PB3); also elsewhere on the board
SWCLK: U1.38 (PA14); also elsewhere on the board
SWDIO: U1.37 (PA13); also elsewhere on the board
TP_TIMING: U1.17 (PB1); also elsewhere on the board
UART_RX_MCU: U1.25 (PB11); also elsewhere on the board
UART_TX_MCU: U1.22 (PB10); also elsewhere on the board

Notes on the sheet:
U1 pin assignment follows hardware/dev-board/cubemx/CubeMX.ioc
